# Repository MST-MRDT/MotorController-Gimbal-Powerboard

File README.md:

# MotorController-Gimbal-Powerboard

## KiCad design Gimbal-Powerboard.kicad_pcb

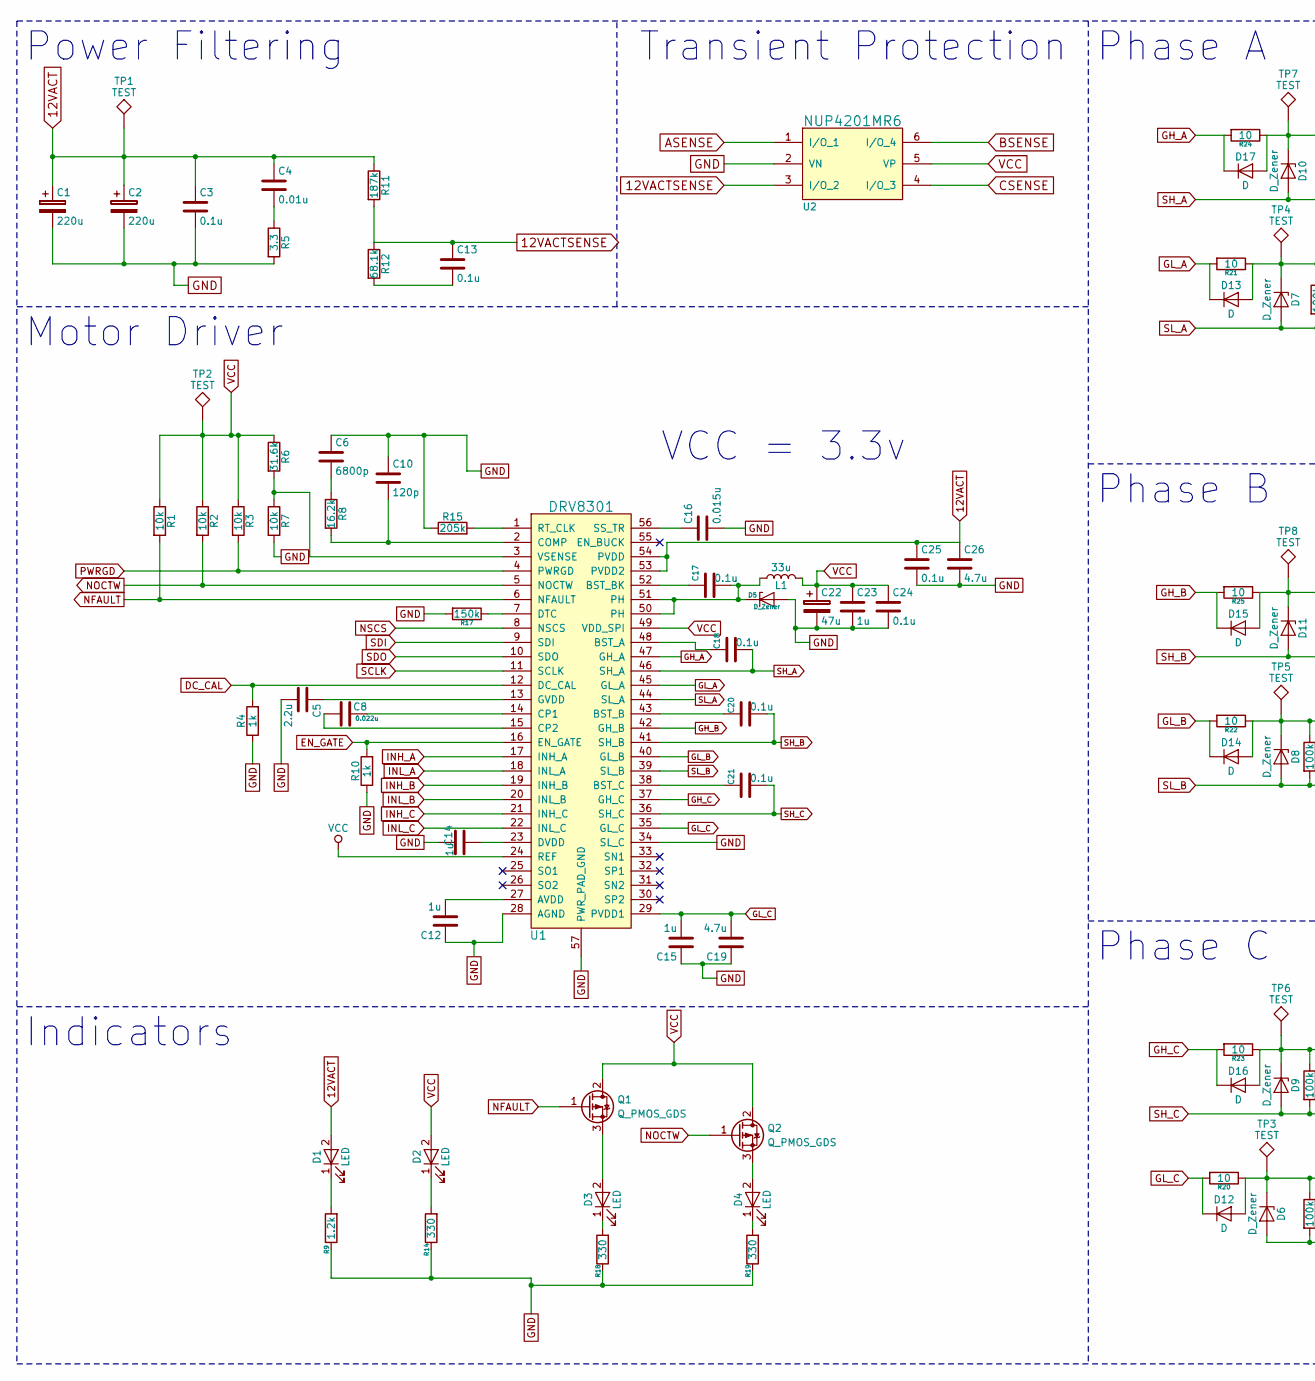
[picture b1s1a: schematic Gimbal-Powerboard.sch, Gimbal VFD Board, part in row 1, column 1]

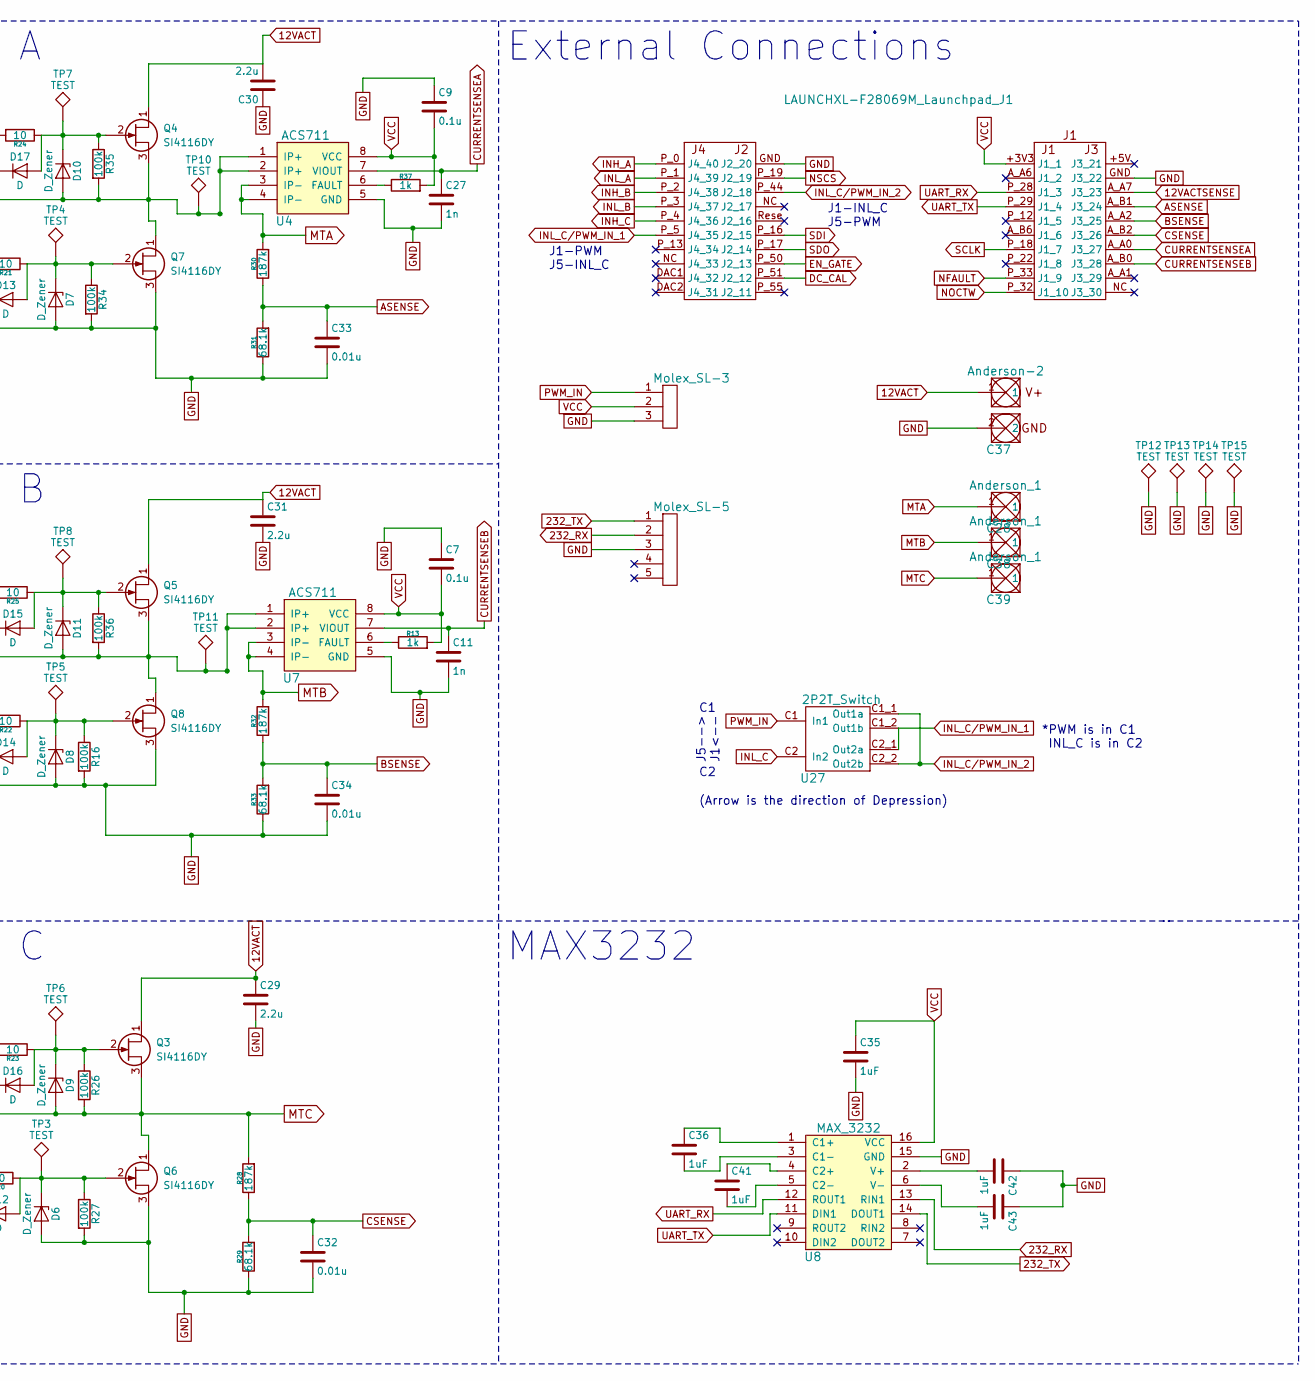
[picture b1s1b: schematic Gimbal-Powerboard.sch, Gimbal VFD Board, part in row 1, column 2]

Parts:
C1, C2: 220u; CP_Radial_D12.5mm_P5.00mm
C3, C7, C9, C13, C17, C18, C20, C21, C24, C25: 0.1u; C_0603_HandSoldering
C4, C32, C33, C34: 0.01u; C_0603_HandSoldering
C5, C29, C30, C31: 2.2u; C_1206_HandSoldering
C6: 6800p; C_0603_HandSoldering
C8: 0.022u; C_0603_HandSoldering
C10: 120p; C_0603_HandSoldering
C11, C27: 1n; C_0603_HandSoldering
C12, C14, C15, C23: 1u; C_0603_HandSoldering
C16: 0.015u; C_0603_HandSoldering
C19: 4.7u; C_1206_HandSoldering
C22: 47u; C_1206_HandSoldering
C26: 4.7u; C_0603_HandSoldering
C28, C38, C39: Anderson_1; Anderson_1_Horisontal
C35, C36, C41, C42, C43: 1uF; C_0603_HandSoldering
C37: Anderson-2; Anderson_2_Horisontal_Side_by_Side
D1, D2, D3, D4: LED; LED_1206_HandSoldering
D5, D6, D7, D8, D9, D10, D11: D_Zener; D_SOD-323_HandSoldering
D12, D13, D14, D15, D16, D17: D; D_SOD-123
L1: 33u; DR74_330_R
Q1, Q2: Q_PMOS_GDS; SOT-23_Handsoldering
Q3, Q4, Q5, Q6, Q7, Q8: SI4116DY; SO-8_N_Si4116dy_nChannelMOSFET
R1, R2, R3, R7: 10k; C_0603_HandSoldering
R4, R10, R13, R37: 1k; C_0603_HandSoldering
R5: 3.3; C_0603_HandSoldering
R6: 31.6k; C_0603_HandSoldering
R8: 16.2k; C_0603_HandSoldering
R9: 1.2k; C_0603_HandSoldering
R11, R28, R30, R32: 187k; C_0603_HandSoldering
R12, R29, R31, R33: 68.1k; C_0603_HandSoldering
R14, R18, R19: 330; C_0603_HandSoldering
R15: 205k; C_0603_HandSoldering
R16, R26, R27, R34, R35, R36: 100k; C_0603_HandSoldering
R17: 150k; C_0603_HandSoldering
R20, R21, R22, R23, R24, R25: 10; C_0603_HandSoldering
TP1, TP2, TP3, TP4, TP5, TP6, TP7, TP8, TP10, TP11, TP12, TP13, TP14, TP15: TEST; SolderWirePad_single_1mmDrill
U1: DRV8301
U2: NUP4201MR6
U3: LAUNCHXL-F28069M_Launchpad_J1; LAUNCHXL_F28069M_Launchpad_J1_BottomSMD
U4, U7: ACS711; SOIC127P600X175-8N
U5: Molex_SL-3; MOLEX_SL_3_Horizontal
U6: Molex_SL-5; MOLEX_SL_5_Horizontal
U8: MAX_3232; SOIC_16_3.9x9.9mm_Pitch1.27mm
U27: 2P2T_Switch; 2P2T_Switch_GrayHill_Series76

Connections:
12VACT: C1.1, C2.1, C3.1, C4.1, C25.1, C26.1, C29.1, C30.2, C31.1, C37.1, D1.2 (A), Q3.1 (D), Q4.1 (D), Q5.1 (D), R11.1, TP1.1, U1.53 (PVDD2), U1.54 (PVDD)
12VACTSENSE: C13.1, R11.2, R12.1, U2.3 (I/O_2), U3.A_A7 (J3_23)
232_RX: U6.2, U8.13 (RIN1)
232_TX: U6.1, U8.14 (DOUT1)
ASENSE: C33.1, R30.1, R31.2, U2.1 (I/O_1), U3.A_B1 (J3_24)
BSENSE: C34.1, R32.1, R33.2, U2.6 (I/O_4), U3.A_A2 (J3_25)
CSENSE: C32.1, R28.1, R29.2, U2.4 (I/O_3), U3.A_B2 (J3_26)
CURRENTSENSEA: C27.1, U3.A_A0 (J3_27), U4.7 (VIOUT)
CURRENTSENSEB: C11.1, U3.A_B0 (J3_28), U7.7 (VIOUT)
DC_CAL: R4.2, U1.12 (DC_CAL), U3.P_51 (J2_12)
DE: U3.P_13 (J4_34)
EN_GATE: R10.2, U1.16 (EN_GATE), U3.P_50 (J2_13)
GH_A: D17.1 (K), R24.2, U1.47 (GH_A)
GH_B: D15.1 (K), R25.2, U1.42 (GH_B)
GH_C: D16.1 (K), R23.2, U1.37 (GH_C)
GL_A: D13.1 (K), R21.2, U1.45 (GL_A)
GL_B: D14.1 (K), R22.2, U1.40 (GL_B)
GL_C: C15.2, C19.2, D12.1 (K), R20.2, U1.29 (PVDD1), U1.35 (GL_C)
GND: C1.2, C2.2, C3.2, C5.2, C6.1, C7.1, C9.1, C10.1, C11.2, C12.1, C14.2, C15.1, C16.2, C19.1, C22.2, C23.2, C24.2, C25.2, C26.2, C27.2, C29.2, C30.1, C31.2, C32.2, C33.2, C34.2, C35.2, C37.2, C42.1, C43.1, D5.2 (A), D6.2 (A), D7.2 (A), D8.2 (A), Q6.3 (S), Q7.3 (S), Q8.3 (S), R4.1, R5.2, R7.2, R9.1, R10.1, R14.1, R15.1, R16.2, R17.2, R18.1, R19.1, R27.2, R29.1, R31.1, R33.1, R34.2, TP12.1, TP13.1, TP14.1, TP15.1, U1.28 (AGND), U1.34 (SL_C), U1.39 (SL_B), U1.44 (SL_A), U1.57 (PWR_PAD_GND), U2.2 (VN), U3.GND (J2_20), U4.5 (GND), U5.3, U6.3, U7.5 (GND), U8.15 (GND)
INH_A: U1.17 (INH_A), U3.P_0 (J4_40)
INH_B: U1.19 (INH_B), U3.P_2 (J4_38)
INH_C: U1.21 (INH_C), U3.P_4 (J4_36)
INL_A: U1.18 (INL_A), U3.P_1 (J4_39)
INL_B: U1.20 (INL_B), U3.P_3 (J4_37)
INL_C: U1.22 (INL_C), U27.C2 (In2)
INL_C/PWM_IN_1: U3.P_5 (J4_35), U27.C1_2 (Out1b), U27.C2_1 (Out2a)
INL_C/PWM_IN_2: U3.P_44 (J2_18), U27.C1_1 (Out1a), U27.C2_2 (Out2b)
MTA: C28.1, R30.2, U4.3 (IP-), U4.4 (IP-)
MTB: C38.1, R32.2, U7.3 (IP-), U7.4 (IP-)
MTC: C21.2, C39.1, D9.2 (A), Q3.3 (S), Q6.1 (D), R26.2, R28.2, U1.36 (SH_C)
NFAULT: Q1.1 (G), R1.2, U1.6 (NFAULT), U3.P_33 (J1_9)
NOCTW: Q2.1 (G), R2.2, U1.5 (NOCTW), U3.P_32 (J1_10)
NSCS: U1.8 (NSCS), U3.P_19 (J2_19)
unnamed: C4.2, R5.1
unnamed: C5.1, U1.13 (GVDD)
unnamed: C6.2, R8.1
unnamed: C8.1, U1.14 (CP1)
unnamed: C8.2, U1.15 (CP2)
unnamed: C10.2, R8.2, U1.2 (COMP)
unnamed: C12.2, U1.27 (AVDD)
unnamed: C13.2, R12.2
unnamed: C14.1, U1.23 (DVDD)
unnamed: C16.1, U1.56 (SS_TR)
unnamed: C17.1, U1.52 (BST_BK)
unnamed: C17.2, D5.1 (K), L1.1, U1.50 (PH), U1.51 (PH)
unnamed: C18.1, U1.48 (BST_A)
unnamed: C20.1, U1.43 (BST_B)
unnamed: C21.1, U1.38 (BST_C)
unnamed: C36.1, U8.1 (C1+)
unnamed: C36.2, U8.3 (C1-)
unnamed: C41.1, U8.4 (C2+)
unnamed: C41.2, U8.5 (C2-)
unnamed: C42.2, U8.2 (V+)
unnamed: C43.2, U8.6 (V-)
unnamed: D1.1 (K), R9.2
unnamed: D2.1 (K), R14.2
unnamed: D3.1 (K), R18.2
unnamed: D3.2 (A), Q1.3 (S)
unnamed: D4.1 (K), R19.2
unnamed: D4.2 (A), Q2.3 (S)
unnamed: D10.1 (K), D17.2 (A), Q4.2 (G), R24.1, R35.1, TP7.1
unnamed: D11.1 (K), D15.2 (A), Q5.2 (G), R25.1, R36.1, TP8.1
unnamed: D6.1 (K), D12.2 (A), Q6.2 (G), R20.1, R27.1, TP3.1
unnamed: D7.1 (K), D13.2 (A), Q7.2 (G), R21.1, R34.1, TP4.1
unnamed: D8.1 (K), D14.2 (A), Q8.2 (G), R16.1, R22.1, TP5.1
unnamed: D9.1 (K), D16.2 (A), Q3.2 (G), R23.1, R26.1, TP6.1
unnamed: R6.2, R7.1, U1.3 (VSENSE)
unnamed: R13.1, U7.6 (FAULT)
unnamed: R15.2, U1.1 (RT_CLK)
unnamed: R17.1, U1.7 (DTC)
unnamed: R37.1, U4.6 (FAULT)
PWM_IN: U5.1, U27.C1 (In1)
PWRGD: R3.2, U1.4 (PWRGD)
SCLK: U1.11 (SCLK), U3.P_18 (J1_7)
SDI: U1.9 (SDI), U3.P_16 (J2_15)
SDO: U1.10 (SDO), U3.P_17 (J2_14)
SH_A: C18.2, D10.2 (A), Q4.3 (S), Q7.1 (D), R35.2, TP10.1, U1.46 (SH_A), U4.1 (IP+), U4.2 (IP+)
SH_B: C20.2, D11.2 (A), Q5.3 (S), Q8.1 (D), R36.2, TP11.1, U1.41 (SH_B), U7.1 (IP+), U7.2 (IP+)
UART_RX: U3.P_28 (J1_3), U8.12 (ROUT1)
UART_TX: U3.P_29 (J1_4), U8.11 (DIN1)
VCC: C7.2, C9.2, C22.1, C23.1, C24.1, C35.1, D2.2 (A), L1.2, Q1.2 (D), Q2.2 (D), R1.1, R2.1, R3.1, R6.1, R13.2, R37.2, TP2.1, U1.24 (REF), U1.49 (VDD_SPI), U2.5 (VP), U3.+3V3 (J1_1), U4.8 (VCC), U5.2, U7.8 (VCC), U8.16 (VCC)

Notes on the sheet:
Power Filtering
Transient Protection
Motor Driver
VCC = 3.3v
Phase A
Phase B
Phase C
Indicators
External Connections
MAX3232
J5--> J1<--
J1-INL_C J5-PWM
J1-PWM J5-INL_C
(Arrow is the direction of Depression)
*PWM is in C1 INL_C is in C2

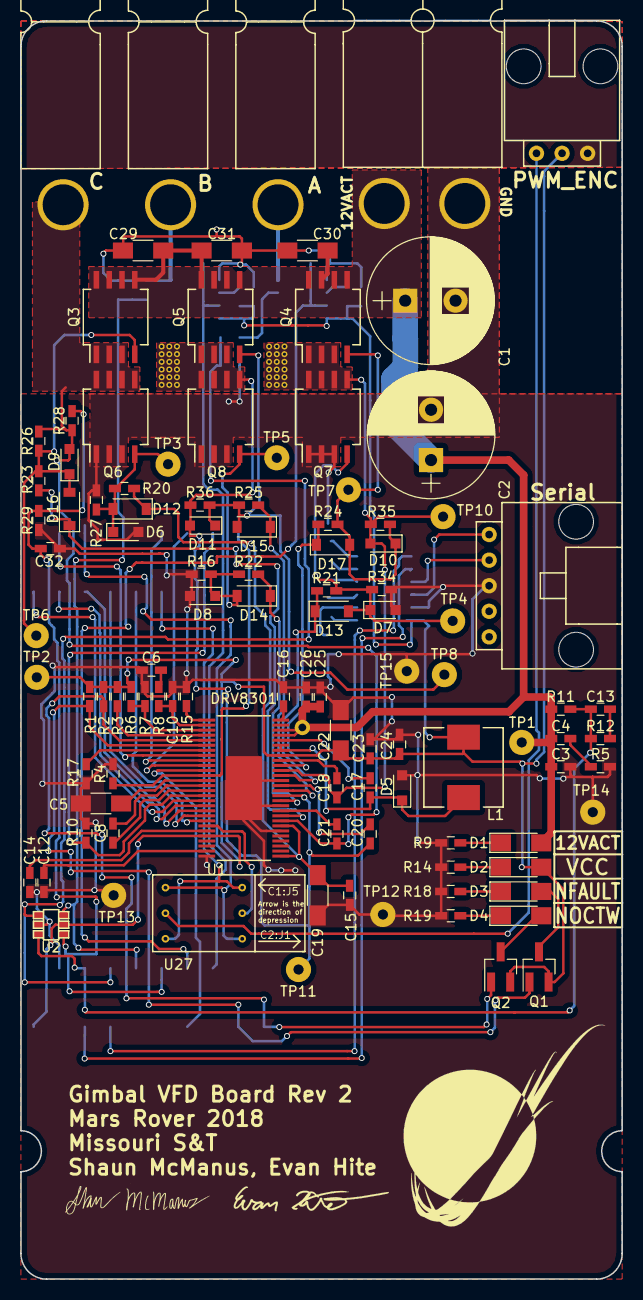
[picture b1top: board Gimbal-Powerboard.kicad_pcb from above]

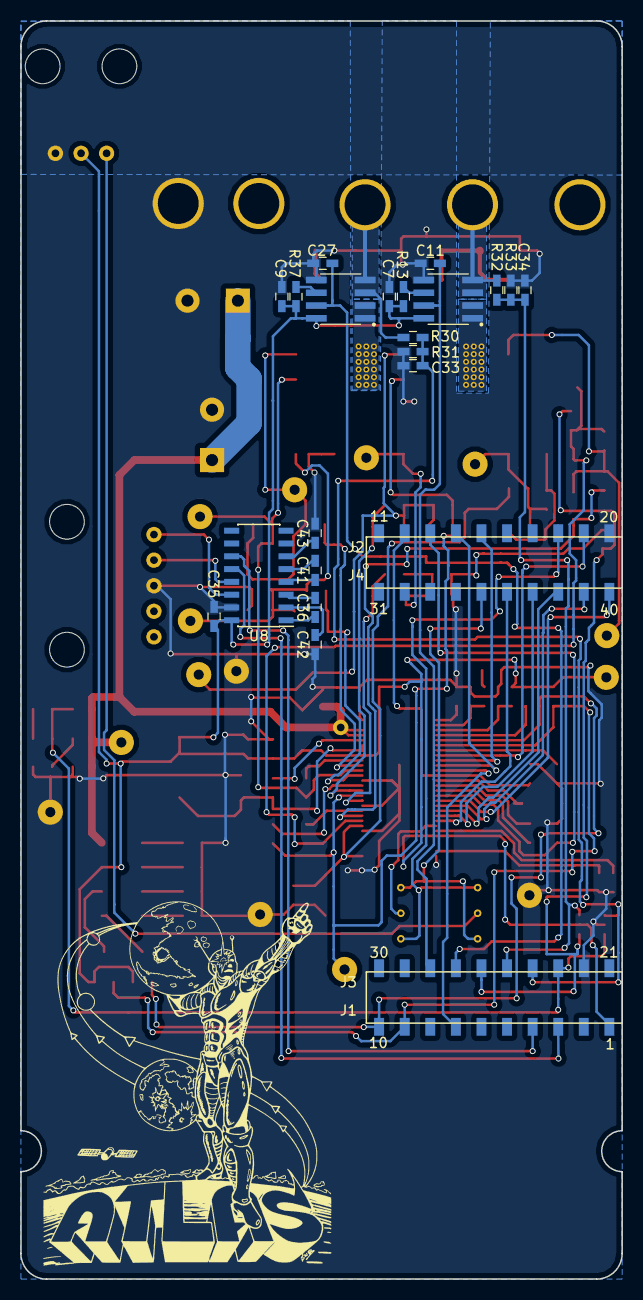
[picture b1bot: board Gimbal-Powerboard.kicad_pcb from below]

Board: 2 copper layers, 59.7 x 124.9 mm, 129 parts (20 on the bottom side), 80 nets.

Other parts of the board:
TP9: TEST; SolderWirePad_single_1mmDrill

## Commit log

2017-11-05 initial commit with Cameron's reference
2017-11-08 changed power filtering cap count and R26 value for 12v to 3.3v conversion
2017-11-10 added CSD18533Q5A fets to Phase C in place of previously used fets
2017-11-10 added CSD18533Q5A fets to Phase B in place of the previously used fets
2017-11-10 added CSD18533Q5A fets to Phase A in place of previously used fets. Cleaned up schematic.
2017-11-10 adjusted phase resistor values for 12v to 3.3v voltage divider
2017-11-10 removed hall effect sensor connector
2017-11-10 Shrank size to roughly 11 square inches, moved lots of components and ripped up wires
2017-11-10 Add pwm connector to external connections
2017-11-10 Started routing traces on board
2017-11-12 Updated silkscreen by removing hall effect sensor indicator and Cameron's signature, mounting holes were squared and board was straightened
2017-11-16 Testing a new board layout by moving the fets and andersons to the right of the board. MAX3232 has also been moved to the left closer to its connector
2017-11-16 Finished arranging test points, beginning traces
2017-11-16 Started Routing
    Connected a lot of components and have started the routing process
2017-11-26 Routed traces for external connections, caps, and a few diodes. Most traces completed except for fet traces.
2017-11-26 Finished Tracing
    All clearance issues have been fixed. The board's tracing issues have been fixed. All overlap issues have been fixed. It is now ready for Board Review.
2017-11-26 Shrank Board
    Board is now smaller
2017-11-30 Smashed and Via Patched the Board
    Almost every surface mount now has a via connecting it to the other three ground plains. Silkscreen is a WIP.
2017-11-30 Silk Screen Improvement
2017-12-01 Updated silkscreen and moved a cap
    Made some slight clarity changes for better readability
2017-12-04 Updated Board
    Now board is updated
2017-12-04 Board Updated for Board Review
2017-12-18 Fixed certain silkscreen issues and routing
    LED's are now fully labelled and in easy to see places
2017-12-18 Forgot to include the schematic for the board
2017-12-22 Changed Resistor values for 15v to 3.3v conversion.
    Changed resistor values for 15v to 3.3v conversion. Bumped up the magnitude by 10x per board review #1 suggestions.
2017-12-23 Changed Fets Around and redid routing
    Fets are now ABC, instead of CBA. This made for easier routing. Silkscreen is updated and the LED's are properly labelled. FET models are still unchanged. Routing has been cleaned up to the best of m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
2017-12-23 Reorganized schematic sections
    Added new section for MAX232 and reorganized External connections for clarity
2017-12-23 Edited label size for neatness and consistency
2017-12-29 Moved Max232 to avoid bridging with SL connectors
2018-01-14 Added new FET package, reorganized schematic to further clean up the labeling
2018-01-15 Updated resistor values to give 3.2v/15v ratio with resistors known to be available on digikey with the 0805 package
2018-01-15 Added Vertical Mounting Wing. Integrated New Fets adjusted andersons for Control Card
    0.5 Inches of the Board has been added for a vertical mounting wing. Routing for new fets has been made. Board has been increased in size significantly. Basic Silkscreen adjustments have been made. B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
2018-01-21 Added Vertical mounting wing
2018-01-21 Fixed ERC issue
2018-01-22 Updated resistor values for new divider, updated indicators section, changed PWM_IN_NO_FILTER to PWM_IN and removed previous PWM_IN label
    Resistor values updated for 12v to 3.2v ratio. Simplified D6 indicator schematic to be just an LED, resistor, power, and ground. Changed old PWM_IN_NO_FILTER label to PWM_IN in external connections, 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
2018-01-22 Board routing was cleaned up. Silkscreen was cleaned up. Correct Package for Power Anderson Connectors is now being used.
    Mounting holes were removed. SL connectors were labelled. All test points are correctly named. More vias have been added to stitch the planes together. Traces were redrawn in many places for cleaner 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
2018-01-22 Silscreen Update
    Added arrows to aid in putting cards together.
2018-01-23 Silkscreen Update and Dimension update
    Silkscreen was added for the inductor as well as all the Fets. Dimension of the board was alterred to accomodate a vertical mount with extra headroom to prevent any mechanical complications.
2018-01-24 Another Silkscreen update
    LED's silkscreen was added for better visibility.
2018-01-25 Added a bill of materials
2018-01-25 Fixed LED positions
2018-01-28 Vertical Mounting drill hole size increased
2018-01-29 Added Signatures and BOM file is now text file
2018-03-11 Initial upload of KiCAD Gimbal Powerboard
2018-03-11 Replaced legacy LaunchXL headers with new LaunchXL header device in schematic
2018-03-11 Github Fix Commit
2018-03-11 Removed outdated BOM
2018-03-11 Removed gitignore and properly added .pro file
2018-03-14 Started device/package pairing
2018-03-14 Paired devices and packages for all components of schematic except MAX3232
2018-03-14 Finished pairing devices with packages and generated netlist
2018-03-14 Added preliminary adjustments for current sensor implementation
2018-03-18 Added current sensor
2018-04-01 Added netlist, updated drv8301 implementation
2018-04-01 Adjusted circuit implementation of DRV8301, adjusted FETs for LED indicators to have correct orientation for pads
2018-04-01 Finished troubleshooting all netlist read errors, final push before board construction
2018-04-01 Final netlist
2018-04-08 Changed MAX3232 device, updated GND and VCC flags, added 100k pull down resistor in parallel with zener diode, added diode across 10 ohm resistor for all phases, added flags for motor terminal A,B,C
2018-04-09 Initial PCB layout with 2P2T switch for PWM, INL_C
2018-04-12 Sorted PCB components, preliminary layout
2018-04-13 Created traces for MAX3232, part of DRV8301
2018-04-13 Finished component placement for DRV8301, phase C
2018-04-14 Added components for phase B circuitry
2018-04-14 Finished component placement, beginning the last of traces and silkscreen work
2018-04-14 Finished routing for DRV8301
2018-04-14 More routing progress, most of the top third of the board is completed
2018-04-15 Finished all routing
2018-04-15 Added silkscreen for indicator LEDs and 2P2T switch
2018-04-15 Added ground copper layer, silkscreen for serial, pwm, phase connections, removed test point for MTC. Finished round 1 board review with Judah, Andrew, Jacob
2018-04-15 Updated footprint for Tiva SMD J1 header shield
2018-04-16 Updated flags to be directional
2018-04-16 Generated gerbs
2018-04-16 Final gerb generation
2018-04-16 Updated tiva shield with fixed version, generated fresh gerbs
2018-04-18 Added Atlas Logo!
2018-04-18 Made some quick fixes to the silkscreen after quintuple checking the gerbs
2018-04-18 Fixed an issue with drill holes not rendering properly in gerb viewers. Generated fixed gerbs and updated the zip file
2018-04-18 Made some last minute adjustments to the silkscreen for clarity

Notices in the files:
parts and their libraries:
Copyright 2016 Accelerated Designs. All rights reserved.
